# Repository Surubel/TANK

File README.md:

# TANK
Atmega328 with TB6612 motor driver

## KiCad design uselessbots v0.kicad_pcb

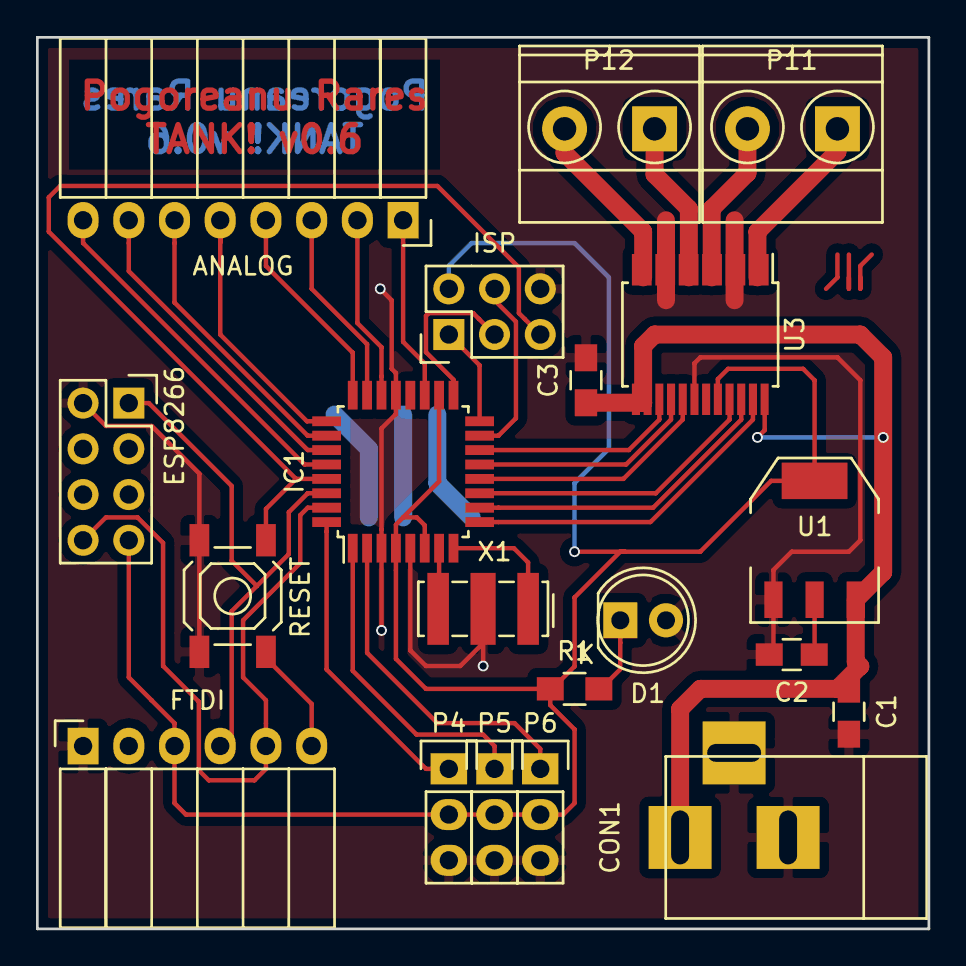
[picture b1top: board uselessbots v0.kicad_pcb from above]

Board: 2 copper layers, 49.5 x 49.5 mm, 20 parts (0 on the bottom side), 31 nets.

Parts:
ANALOG: CONN_01X08; Socket_Strip_Angled_1x08
C1: 100nF; C_0805_HandSoldering
C2, C3: 10uF; C_0805_HandSoldering
CON1: BARREL_JACK
D1: LED; LED-5MM
ESP8266: ESP-01v090; Socket_Strip_Straight_2x04
FTDI: CONN_01X06; Socket_Strip_Angled_1x06
IC1: ATMEGA328P-A; TQFP-32_7x7mm_Pitch0.8mm
ISP: AVR-ISP-6; Pin_Header_Straight_2x03
P4, P5, P6: CONN_01X03; Pin_Header_Straight_1x03
P11, P12: CONN_01X02; TerminalBlock_Pheonix_MKDS1.5-2pol
R1: 1K; R_0805_HandSoldering
RESET: SW_PUSH; SW_SPST_SKQG
U1: LD1117S33TR; SOT-223
U3: TB6612FNG; SSOP-24_5.3x8.2mm_Pitch0.65mm
X1: CRYSTAL_SMD; Resonator_7.2x3mm

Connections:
+3V3: C2.1, ESP8266.7, FTDI.3, IC1.4, IC1.6, IC1.18, ISP.2, P4.2, P5.2, P6.2, R1.1, U1.2, U1.4, U3.20
/A0: ANALOG.3, IC1.23
/A1: ANALOG.4, IC1.11, IC1.24, U3.21
/A2: ANALOG.5, IC1.10, IC1.25, U3.22
/A3: ANALOG.6, IC1.26
/A4: ANALOG.7, IC1.27
/A5: ANALOG.8, IC1.28
/ADC6: ANALOG.1, IC1.19
/ADC7: ANALOG.2, IC1.22
/B1: IC1.12, U3.17
/B2: IC1.13, U3.16
/BATT+: C1.1, C3.1, CON1.1, U1.3, U3.13, U3.14, U3.24
/MISO: IC1.16, ISP.1
/MOSI: IC1.15, ISP.4
/PIN2: IC1.32, P4.1
/PIN3: IC1.1, P5.1
/PIN4: IC1.2, P6.1
/PWMA: IC1.9, U3.23
/PWMB: IC1.14, U3.15
/RESET: FTDI.6, IC1.29, ISP.5, RESET.2
/RX: ESP8266.1, FTDI.4, IC1.30
/SCK: IC1.17, ISP.3
/TX: ESP8266.8, FTDI.5, IC1.31
/XTAL1: IC1.7, X1.3
/XTAL2: IC1.8, X1.1
GND: C1.2, C2.2, C3.2, CON1.2, CON1.3, D1.2, ESP8266.2, FTDI.1, IC1.3, IC1.5, IC1.21, ISP.6, P4.3, P5.3, P6.3, RESET.1, U1.1, U3.3, U3.4, U3.9, U3.10, U3.18, X1.2
unnamed: D1.1, R1.2
unnamed: P11.1, U3.1, U3.2
unnamed: P11.2, U3.5, U3.6
unnamed: P12.1, U3.7, U3.8
unnamed: P12.2, U3.11, U3.12
